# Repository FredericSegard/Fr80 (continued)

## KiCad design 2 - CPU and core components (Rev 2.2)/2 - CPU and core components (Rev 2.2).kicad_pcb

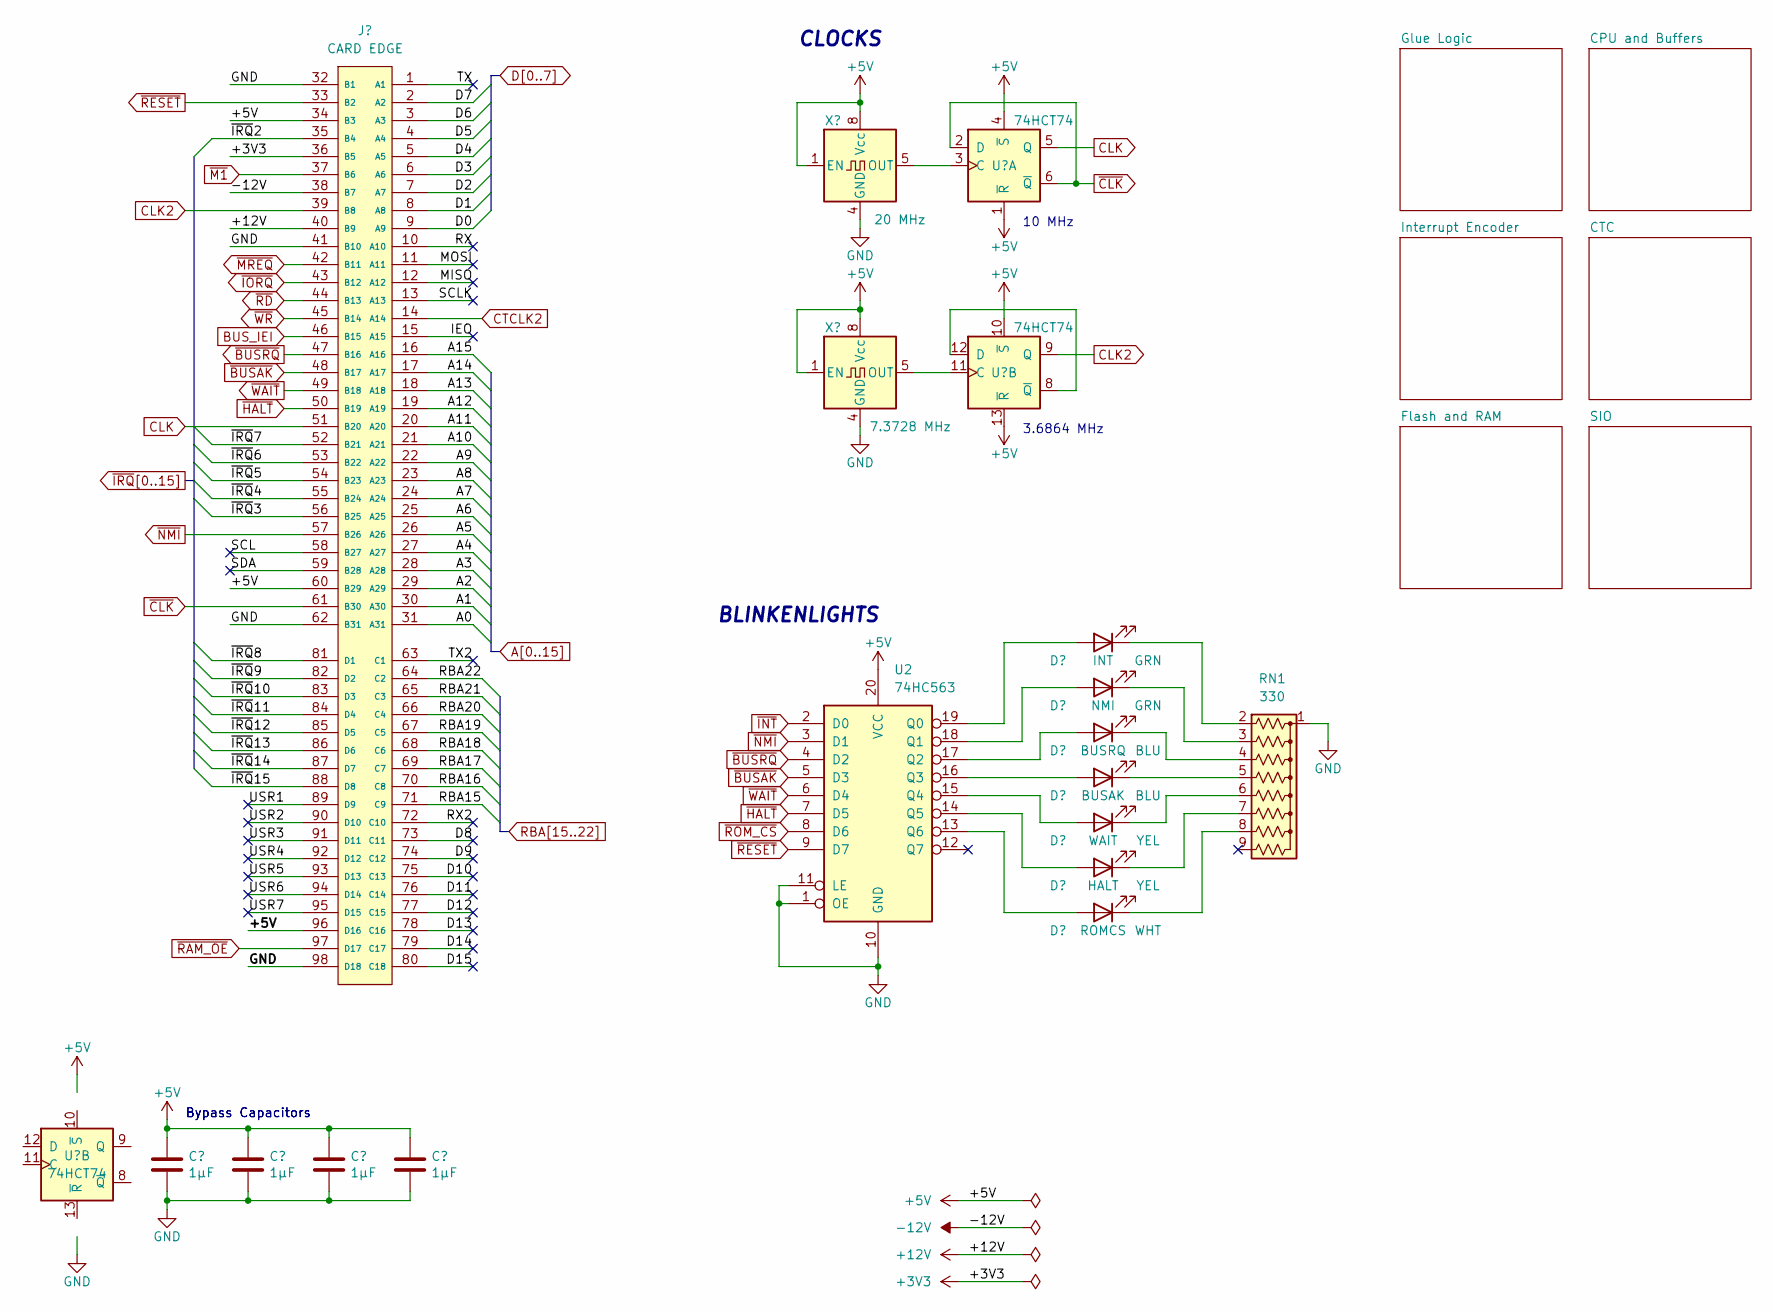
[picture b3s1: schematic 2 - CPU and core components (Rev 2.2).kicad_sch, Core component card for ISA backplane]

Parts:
C1, C2, C3, C4: 1µF; C_Disc_D3.4mm_W2.1mm_P2.50mm
D1: INT; LED_D3.0mm_Horizontal_O1.27mm_Z2.0mm_Clear
D2: NMI; LED_D3.0mm_Horizontal_O1.27mm_Z2.0mm_Clear
D3: BUSRQ; LED_D3.0mm_Horizontal_O1.27mm_Z2.0mm_Clear
D4: BUSAK; LED_D3.0mm_Horizontal_O1.27mm_Z2.0mm_Clear
D5: WAIT; LED_D3.0mm_Horizontal_O1.27mm_Z2.0mm_Clear
D6: HALT; LED_D3.0mm_Horizontal_O1.27mm_Z2.0mm_Clear
D7: ROMCS; LED_D3.0mm_Horizontal_O1.27mm_Z2.0mm_Clear
J1: CARD EDGE; BUS_AT v2
RN1: 330; R_Array_SIP9
U1: 74HCT74; DIP-14_W7.62mm_Socket
U2: 74HC563; DIP-20_W7.62mm_Socket
X1: 20 MHz; DIP-8-4_W7.62mm_Oscillator_Socket
X2: 7.3728 MHz; DIP-8-4_W7.62mm_Oscillator_Socket

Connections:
+3V3: J1.36 (B5)
+5V: C1.1, C2.1, C3.1, C4.1, J1.34 (B3), J1.60 (B29), J1.96 (D16), U1.1 (~R), U1.4 (~S), U1.10 (~S), U1.13 (~R), U1.14 (VCC), U2.20 (VCC), X1.1 (EN), X1.8 (Vcc), X2.1 (EN), X2.8 (Vcc); also elsewhere on the board
+12V: J1.40 (B9)
-12V: J1.38 (B7)
/D8: J1.73 (C11)
/D9: J1.74 (C12)
/D10: J1.75 (C13)
/D11: J1.76 (C14)
/D12: J1.77 (C15)
/D13: J1.78 (C16)
/D14: J1.79 (C17)
/D15: J1.80 (C18)
/IEO: J1.15 (A15)
/MISO: J1.12 (A12)
/MOSI: J1.11 (A11)
/RX: J1.10 (A10)
/RX2: J1.72 (C10)
/SCL: J1.58 (B27)
/SCLK: J1.13 (A13)
/SDA: J1.59 (B28)
/TX: J1.1 (A1)
/TX2: J1.63 (C1)
/USR1: J1.89 (D9)
/USR2: J1.90 (D10)
/USR3: J1.91 (D11)
/USR4: J1.92 (D12)
/USR5: J1.93 (D13)
/USR6: J1.94 (D14)
/USR7: J1.95 (D15)
A0: J1.31 (A31); also elsewhere on the board
A1: J1.30 (A30); also elsewhere on the board
A2: J1.29 (A29); also elsewhere on the board
A3: J1.28 (A28); also elsewhere on the board
A4: J1.27 (A27); also elsewhere on the board
A5: J1.26 (A26); also elsewhere on the board
A6: J1.25 (A25); also elsewhere on the board
A7: J1.24 (A24); also elsewhere on the board
A8: J1.23 (A23); also elsewhere on the board
A9: J1.22 (A22); also elsewhere on the board
A10: J1.21 (A21); also elsewhere on the board
A11: J1.20 (A20); also elsewhere on the board
A12: J1.19 (A19); also elsewhere on the board
A13: J1.18 (A18); also elsewhere on the board
A14: J1.17 (A17); also elsewhere on the board
A15: J1.16 (A16); also elsewhere on the board
BUS_IEI: J1.46 (B15); also elsewhere on the board
CLK: J1.51 (B20), U1.5 (Q); also elsewhere on the board
CLK2: J1.39 (B8), U1.9 (Q); also elsewhere on the board
CTCLK2: J1.14 (A14); also elsewhere on the board
D0: J1.9 (A9); also elsewhere on the board
D1: J1.8 (A8); also elsewhere on the board
D2: J1.7 (A7); also elsewhere on the board
D3: J1.6 (A6); also elsewhere on the board
D4: J1.5 (A5); also elsewhere on the board
D5: J1.4 (A4); also elsewhere on the board
D6: J1.3 (A3); also elsewhere on the board
D7: J1.2 (A2); also elsewhere on the board
GND: C1.2, C2.2, C3.2, C4.2, J1.32 (B1), J1.41 (B10), J1.62 (B31), J1.98 (D18), RN1.1 (common), U1.7 (GND), U2.1 (OE), U2.10 (GND), U2.11 (LE), X1.4 (GND), X2.4 (GND); also elsewhere on the board
unnamed: D1.2 (A), U2.19 (Q0)
unnamed: D1.1 (K), RN1.2 (R1)
unnamed: D2.2 (A), U2.18 (Q1)
unnamed: D2.1 (K), RN1.3 (R2)
unnamed: D3.2 (A), U2.17 (Q2)
unnamed: D3.1 (K), RN1.4 (R3)
unnamed: D4.2 (A), U2.16 (Q3)
unnamed: D4.1 (K), RN1.5 (R4)
unnamed: D5.2 (A), U2.15 (Q4)
unnamed: D5.1 (K), RN1.6 (R5)
unnamed: D6.2 (A), U2.14 (Q5)
unnamed: D6.1 (K), RN1.7 (R6)
unnamed: D7.2 (A), U2.13 (Q6)
unnamed: D7.1 (K), RN1.8 (R7)
unnamed: U1.3 (C), X1.5 (OUT)
unnamed: U1.11 (C), X2.5 (OUT)
unnamed: U1.8 (~Q), U1.12 (D)
RBA15: J1.71 (C9); also elsewhere on the board
RBA16: J1.70 (C8); also elsewhere on the board
RBA17: J1.69 (C7); also elsewhere on the board
RBA18: J1.68 (C6); also elsewhere on the board
RBA19: J1.67 (C5); also elsewhere on the board
RBA20: J1.66 (C4); also elsewhere on the board
RBA21: J1.65 (C3); also elsewhere on the board
RBA22: J1.64 (C2); also elsewhere on the board
~BUSAK: J1.48 (B17), U2.5 (D3); also elsewhere on the board
~BUSRQ: J1.47 (B16), U2.4 (D2); also elsewhere on the board
~CLK: J1.61 (B30), U1.2 (D), U1.6 (~Q)
~HALT: J1.50 (B19), U2.7 (D5); also elsewhere on the board
~INT: U2.2 (D0); also elsewhere on the board
~IORQ: J1.43 (B12); also elsewhere on the board
~IRQ2: J1.35 (B4); also elsewhere on the board
~IRQ3: J1.56 (B25); also elsewhere on the board
~IRQ4: J1.55 (B24); also elsewhere on the board
~IRQ5: J1.54 (B23); also elsewhere on the board
~IRQ6: J1.53 (B22); also elsewhere on the board
~IRQ7: J1.52 (B21); also elsewhere on the board
~IRQ8: J1.81 (D1); also elsewhere on the board
~IRQ9: J1.82 (D2); also elsewhere on the board
~IRQ10: J1.83 (D3); also elsewhere on the board
~IRQ11: J1.84 (D4); also elsewhere on the board
~IRQ12: J1.85 (D5); also elsewhere on the board
~IRQ13: J1.86 (D6); also elsewhere on the board
~IRQ14: J1.87 (D7); also elsewhere on the board
~IRQ15: J1.88 (D8); also elsewhere on the board
~M1: J1.37 (B6); also elsewhere on the board
~MREQ: J1.42 (B11); also elsewhere on the board
~NMI: J1.57 (B26), U2.3 (D1); also elsewhere on the board
~RAM_OE: J1.97 (D17); also elsewhere on the board
~RD: J1.44 (B13); also elsewhere on the board
~RESET: J1.33 (B2), U2.9 (D7); also elsewhere on the board
~ROM_CS: U2.8 (D6); also elsewhere on the board
~WAIT: J1.49 (B18), U2.6 (D4); also elsewhere on the board
~WR: J1.45 (B14); also elsewhere on the board

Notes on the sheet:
10 MHz
Bypass Capacitors
BLINKENLIGHTS
CLOCKS
3.6864 MHz

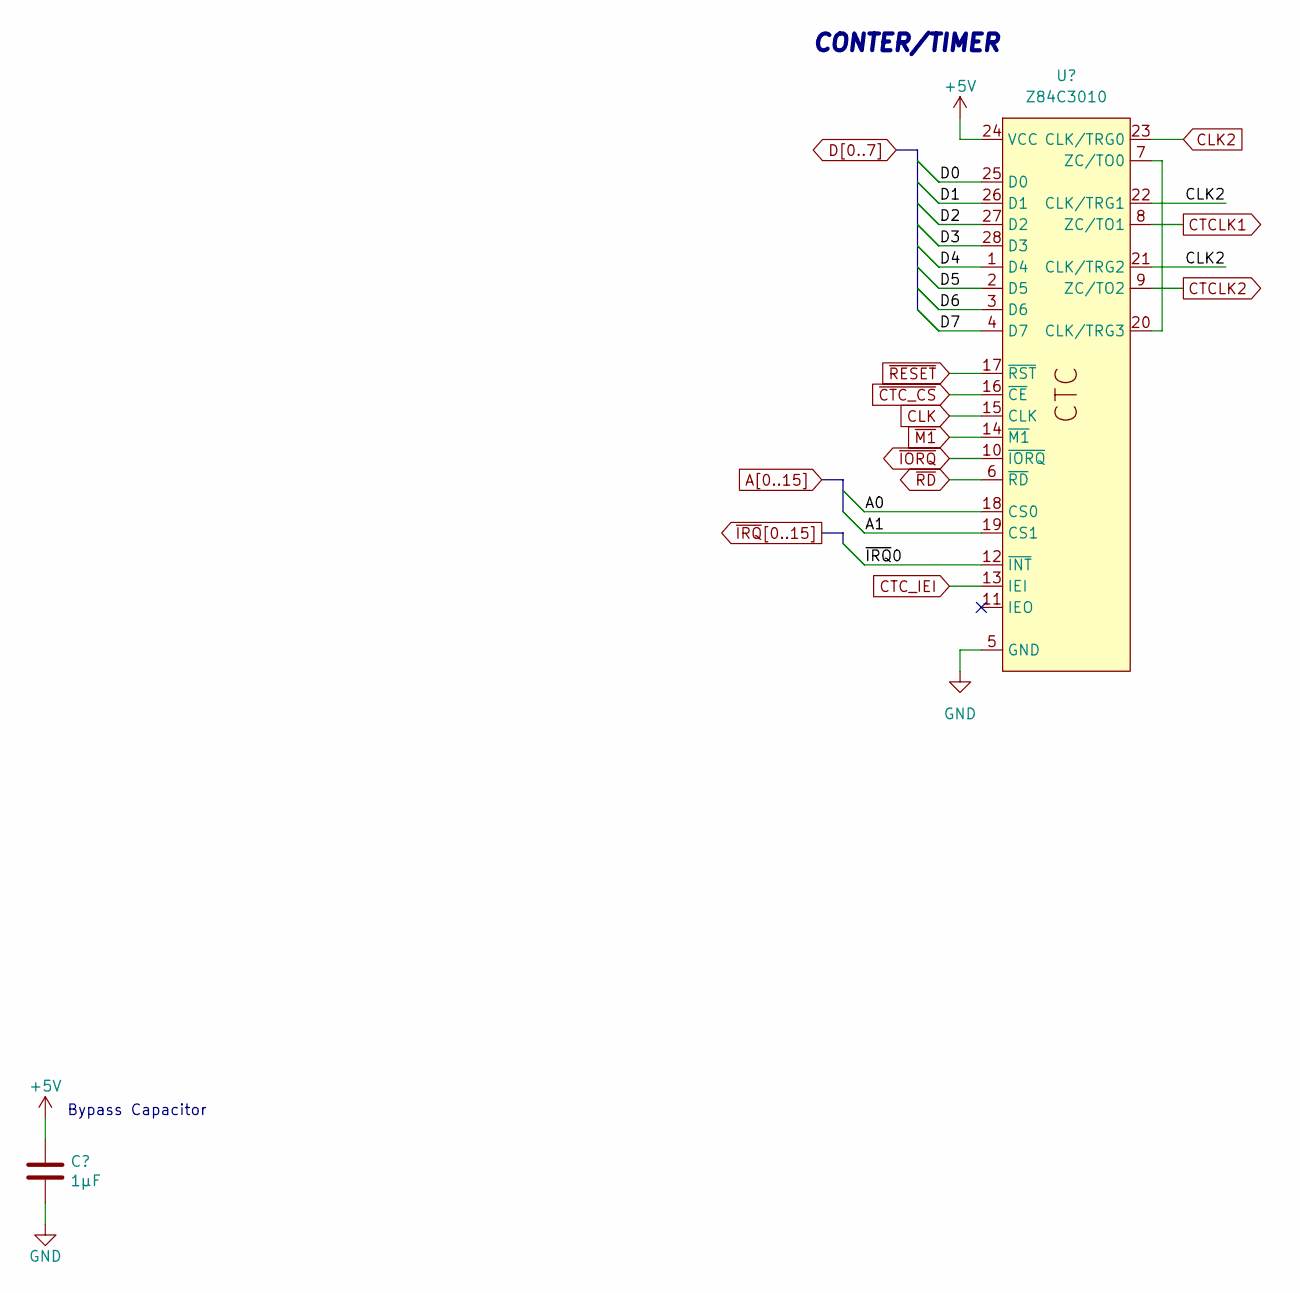
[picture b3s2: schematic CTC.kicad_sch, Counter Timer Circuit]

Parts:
C25: 1µF; C_Disc_D3.4mm_W2.1mm_P2.50mm
U21: Z84C3010; DIP-28_W15.24mm_Socket

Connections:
+5V: C25.1, U21.24 (VCC); also elsewhere on the board
A0: U21.18 (CS0); also elsewhere on the board
A1: U21.19 (CS1); also elsewhere on the board
CLK: U21.15 (CLK); also elsewhere on the board
CLK2: U21.21 (CLK/TRG2), U21.22 (CLK/TRG1), U21.23 (CLK/TRG0); also elsewhere on the board
CTCLK1: U21.8 (ZC/TO1); also elsewhere on the board
CTCLK2: U21.9 (ZC/TO2); also elsewhere on the board
CTC_IEI: U21.13 (IEI); also elsewhere on the board
D0: U21.25 (D0); also elsewhere on the board
D1: U21.26 (D1); also elsewhere on the board
D2: U21.27 (D2); also elsewhere on the board
D3: U21.28 (D3); also elsewhere on the board
D4: U21.1 (D4); also elsewhere on the board
D5: U21.2 (D5); also elsewhere on the board
D6: U21.3 (D6); also elsewhere on the board
D7: U21.4 (D7); also elsewhere on the board
GND: C25.2, U21.5 (GND); also elsewhere on the board
unnamed: U21.7 (ZC/TO0), U21.20 (CLK/TRG3)
~CTC_CS: U21.16 (~CE); also elsewhere on the board
~IORQ: U21.10 (~IORQ); also elsewhere on the board
~IRQ0: U21.12 (~INT); also elsewhere on the board
~M1: U21.14 (~M1); also elsewhere on the board
~RD: U21.6 (~RD); also elsewhere on the board
~RESET: U21.17 (~RST); also elsewhere on the board

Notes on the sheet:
CONTER/TIMER
Bypass Capacitor

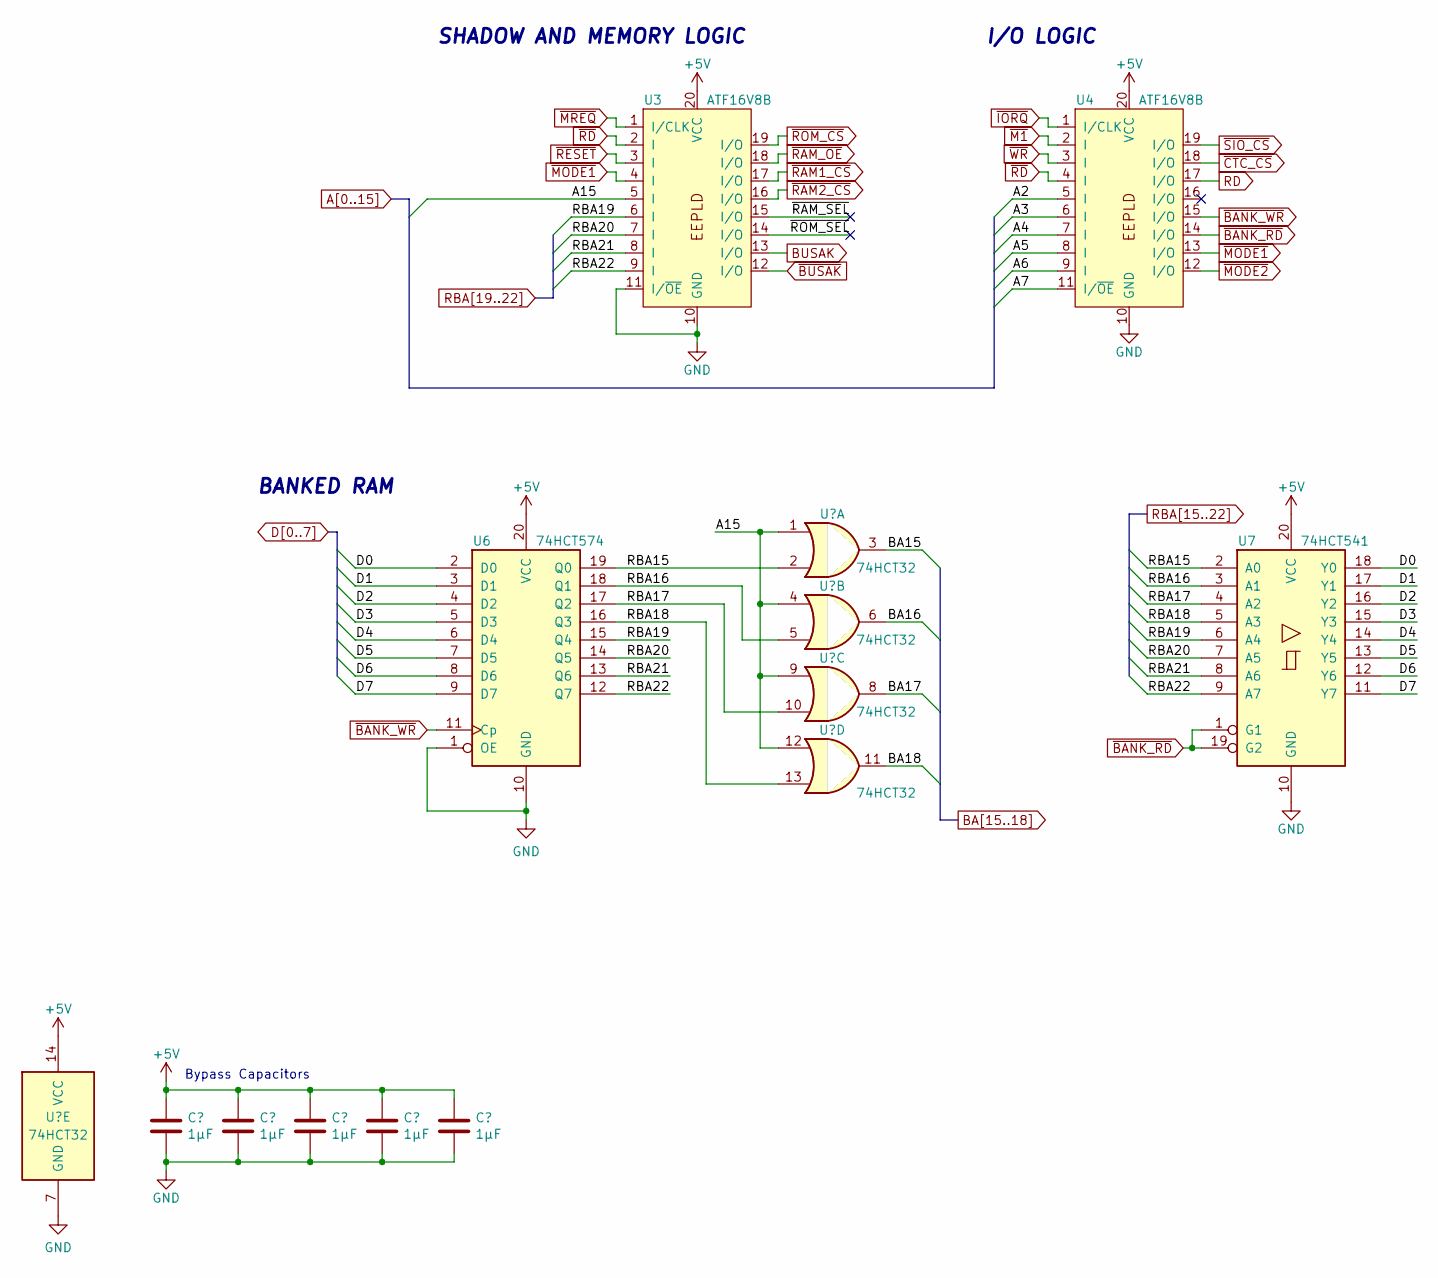
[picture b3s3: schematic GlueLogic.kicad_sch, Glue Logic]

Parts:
C5, C6, C7: 1µF; C_Disc_D3.0mm_W1.6mm_P2.50mm
C8, C9: 1µF; C_Disc_D3.0mm_W2.0mm_P2.50mm
U3, U4: ATF16V8B; DIP-20_W7.62mm_Socket
U5: 74HCT32; DIP-14_W7.62mm_Socket
U6: 74HCT574; DIP-20_W7.62mm_Socket
U7: 74HCT541; DIP-20_W7.62mm_Socket

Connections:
+5V: C5.1, C6.1, C7.1, C8.1, C9.1, U3.20 (VCC), U4.20 (VCC), U5.14 (VCC), U6.20 (VCC), U7.20 (VCC); also elsewhere on the board
/Glue Logic/~RAM_SEL: U3.15 (I/O)
/Glue Logic/~ROM_SEL: U3.14 (I/O)
A2: U4.5 (I); also elsewhere on the board
A3: U4.6 (I); also elsewhere on the board
A4: U4.7 (I); also elsewhere on the board
A5: U4.8 (I); also elsewhere on the board
A6: U4.9 (I); also elsewhere on the board
A7: U4.11 (I/~OE); also elsewhere on the board
A15: U3.5 (I), U5.1, U5.4, U5.9, U5.12; also elsewhere on the board
BA15: U5.3; also elsewhere on the board
BA16: U5.6; also elsewhere on the board
BA17: U5.8; also elsewhere on the board
BA18: U5.11; also elsewhere on the board
BUSAK: U3.13 (I/O); also elsewhere on the board
D0: U6.2 (D0), U7.18 (Y0); also elsewhere on the board
D1: U6.3 (D1), U7.17 (Y1); also elsewhere on the board
D2: U6.4 (D2), U7.16 (Y2); also elsewhere on the board
D3: U6.5 (D3), U7.15 (Y3); also elsewhere on the board
D4: U6.6 (D4), U7.14 (Y4); also elsewhere on the board
D5: U6.7 (D5), U7.13 (Y5); also elsewhere on the board
D6: U6.8 (D6), U7.12 (Y6); also elsewhere on the board
D7: U6.9 (D7), U7.11 (Y7); also elsewhere on the board
GND: C5.2, C6.2, C7.2, C8.2, C9.2, U3.10 (GND), U3.11 (I/~OE), U4.10 (GND), U5.7 (GND), U6.1 (OE), U6.10 (GND), U7.10 (GND); also elsewhere on the board
RBA15: U5.2, U6.19 (Q0), U7.2 (A0); also elsewhere on the board
RBA16: U5.5, U6.18 (Q1), U7.3 (A1); also elsewhere on the board
RBA17: U5.10, U6.17 (Q2), U7.4 (A2); also elsewhere on the board
RBA18: U5.13, U6.16 (Q3), U7.5 (A3); also elsewhere on the board
RBA19: U3.6 (I), U6.15 (Q4), U7.6 (A4); also elsewhere on the board
RBA20: U3.7 (I), U6.14 (Q5), U7.7 (A5); also elsewhere on the board
RBA21: U3.8 (I), U6.13 (Q6), U7.8 (A6); also elsewhere on the board
RBA22: U3.9 (I), U6.12 (Q7), U7.9 (A7); also elsewhere on the board
RD: U4.17 (I/O); also elsewhere on the board
~BANK_RD: U4.14 (I/O), U7.1 (G1), U7.19 (G2)
~BANK_WR: U4.15 (I/O), U6.11 (Cp)
~BUSAK: U3.12 (I/O); also elsewhere on the board
~CTC_CS: U4.18 (I/O); also elsewhere on the board
~IORQ: U4.1 (I/CLK); also elsewhere on the board
~M1: U4.2 (I); also elsewhere on the board
~MODE1: U3.4 (I), U4.13 (I/O); also elsewhere on the board
~MODE2: U4.12 (I/O); also elsewhere on the board
~MREQ: U3.1 (I/CLK); also elsewhere on the board
~RAM1_CS: U3.17 (I/O); also elsewhere on the board
~RAM2_CS: U3.16 (I/O); also elsewhere on the board
~RAM_OE: U3.18 (I/O); also elsewhere on the board
~RD: U3.2 (I), U4.4 (I); also elsewhere on the board
~RESET: U3.3 (I); also elsewhere on the board
~ROM_CS: U3.19 (I/O); also elsewhere on the board
~SIO_CS: U4.19 (I/O); also elsewhere on the board
~WR: U4.3 (I); also elsewhere on the board

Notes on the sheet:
Bypass Capacitors
I/O LOGIC
BANKED RAM
SHADOW AND MEMORY LOGIC

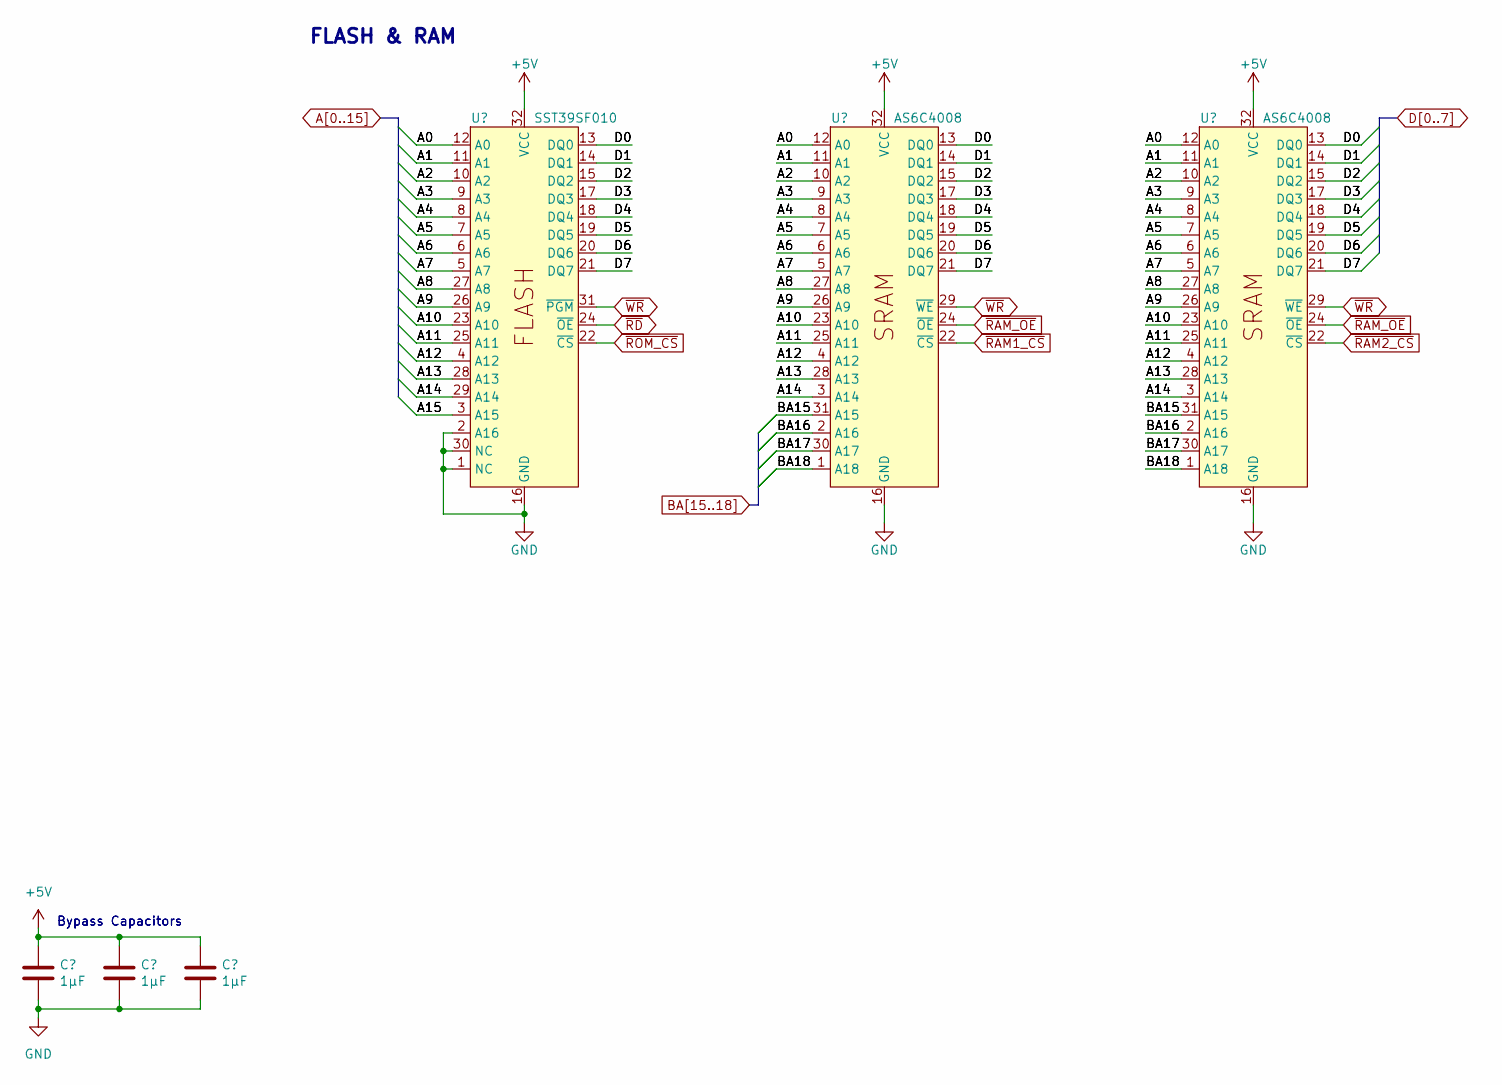
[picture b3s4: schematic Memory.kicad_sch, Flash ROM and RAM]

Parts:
C17, C18, C19: 1µF; C_Disc_D3.4mm_W2.1mm_P2.50mm
U15: SST39SF010; DIP-32_W15.24mm_Socket
U16, U17: AS6C4008; DIP-32_W15.24mm_Socket

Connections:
+5V: C17.1, C18.1, C19.1, U15.32 (VCC), U16.32 (VCC), U17.32 (VCC); also elsewhere on the board
A0: U15.12 (A0), U16.12 (A0), U17.12 (A0); also elsewhere on the board
A1: U15.11 (A1), U16.11 (A1), U17.11 (A1); also elsewhere on the board
A2: U15.10 (A2), U16.10 (A2), U17.10 (A2); also elsewhere on the board
A3: U15.9 (A3), U16.9 (A3), U17.9 (A3); also elsewhere on the board
A4: U15.8 (A4), U16.8 (A4), U17.8 (A4); also elsewhere on the board
A5: U15.7 (A5), U16.7 (A5), U17.7 (A5); also elsewhere on the board
A6: U15.6 (A6), U16.6 (A6), U17.6 (A6); also elsewhere on the board
A7: U15.5 (A7), U16.5 (A7), U17.5 (A7); also elsewhere on the board
A8: U15.27 (A8), U16.27 (A8), U17.27 (A8); also elsewhere on the board
A9: U15.26 (A9), U16.26 (A9), U17.26 (A9); also elsewhere on the board
A10: U15.23 (A10), U16.23 (A10), U17.23 (A10); also elsewhere on the board
A11: U15.25 (A11), U16.25 (A11), U17.25 (A11); also elsewhere on the board
A12: U15.4 (A12), U16.4 (A12), U17.4 (A12); also elsewhere on the board
A13: U15.28 (A13), U16.28 (A13), U17.28 (A13); also elsewhere on the board
A14: U15.29 (A14), U16.3 (A14), U17.3 (A14); also elsewhere on the board
A15: U15.3 (A15); also elsewhere on the board
BA15: U16.31 (A15), U17.31 (A15); also elsewhere on the board
BA16: U16.2 (A16), U17.2 (A16); also elsewhere on the board
BA17: U16.30 (A17), U17.30 (A17); also elsewhere on the board
BA18: U16.1 (A18), U17.1 (A18); also elsewhere on the board
D0: U15.13 (DQ0), U16.13 (DQ0), U17.13 (DQ0); also elsewhere on the board
D1: U15.14 (DQ1), U16.14 (DQ1), U17.14 (DQ1); also elsewhere on the board
D2: U15.15 (DQ2), U16.15 (DQ2), U17.15 (DQ2); also elsewhere on the board
D3: U15.17 (DQ3), U16.17 (DQ3), U17.17 (DQ3); also elsewhere on the board
D4: U15.18 (DQ4), U16.18 (DQ4), U17.18 (DQ4); also elsewhere on the board
D5: U15.19 (DQ5), U16.19 (DQ5), U17.19 (DQ5); also elsewhere on the board
D6: U15.20 (DQ6), U16.20 (DQ6), U17.20 (DQ6); also elsewhere on the board
D7: U15.21 (DQ7), U16.21 (DQ7), U17.21 (DQ7); also elsewhere on the board
GND: C17.2, C18.2, C19.2, U15.1 (NC), U15.2 (A16), U15.16 (GND), U15.30 (NC), U16.16 (GND), U17.16 (GND); also elsewhere on the board
~RAM1_CS: U16.22 (~CS); also elsewhere on the board
~RAM2_CS: U17.22 (~CS); also elsewhere on the board
~RAM_OE: U16.24 (~OE), U17.24 (~OE); also elsewhere on the board
~RD: U15.24 (~OE); also elsewhere on the board
~ROM_CS: U15.22 (~CS); also elsewhere on the board
~WR: U15.31 (~PGM), U16.29 (~WE), U17.29 (~WE); also elsewhere on the board

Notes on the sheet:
Bypass Capacitors
FLASH & RAM

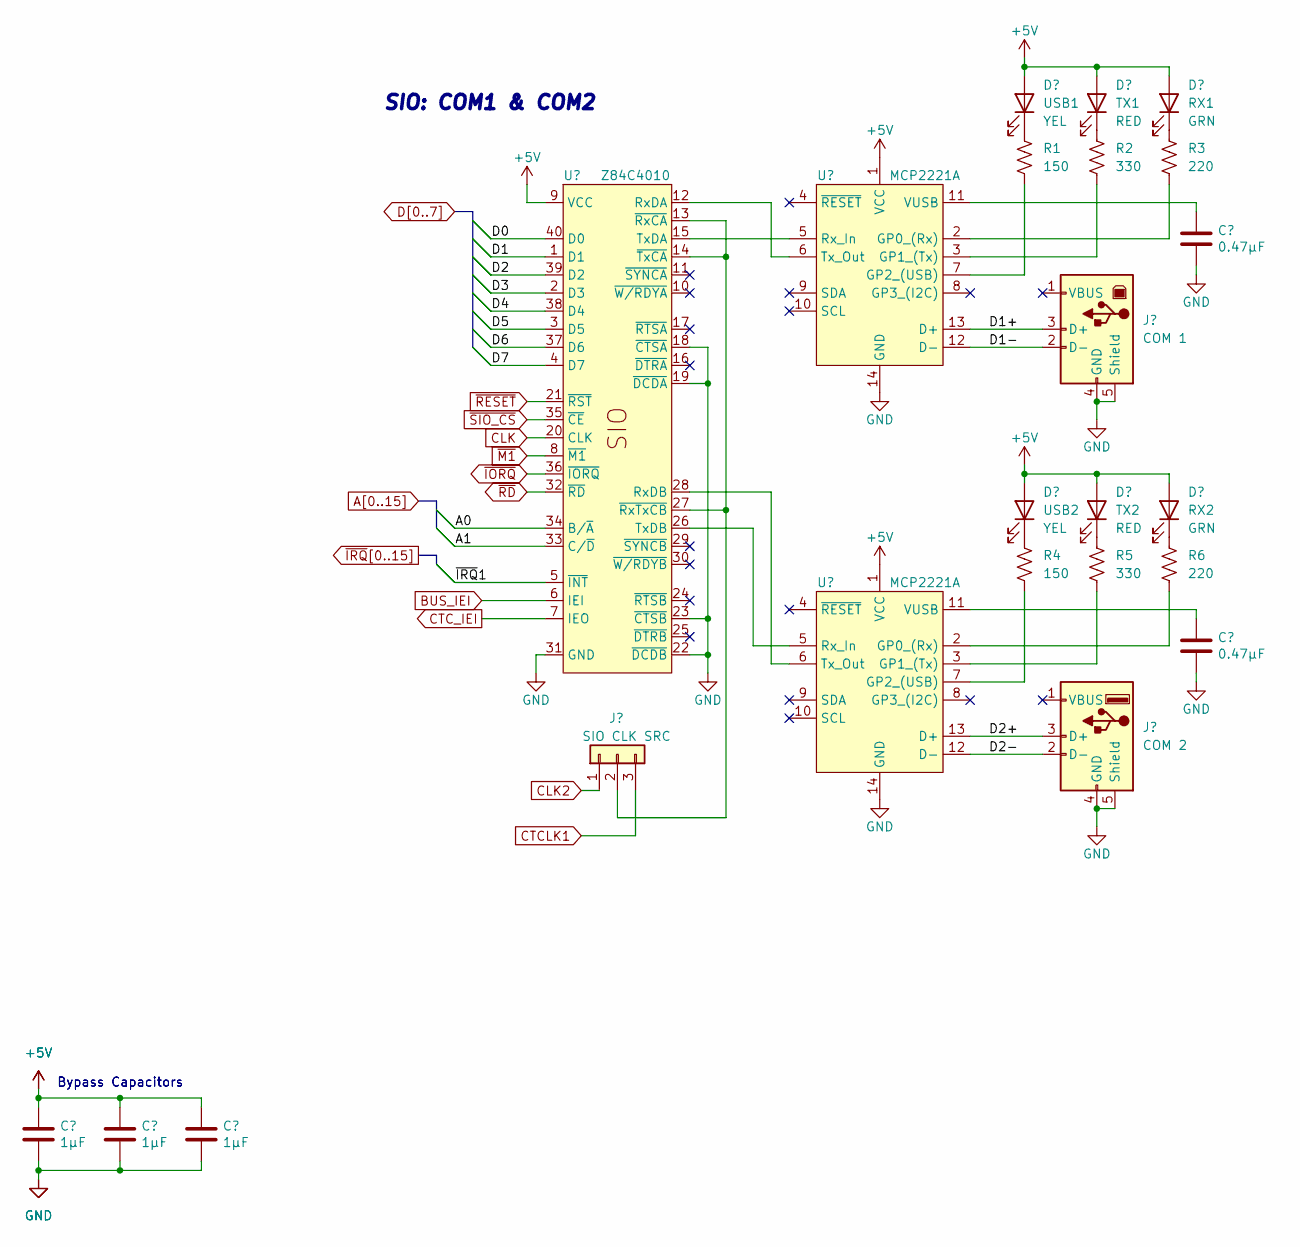
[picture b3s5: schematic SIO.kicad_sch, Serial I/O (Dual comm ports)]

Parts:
C20, C21: 0.47µF; C_Disc_D3.4mm_W2.1mm_P2.50mm
C22, C23, C24: 1µF; C_Disc_D3.4mm_W2.1mm_P2.50mm
D8: USB1; LED_D3.0mm_Horizontal_O1.27mm_Z2.0mm_Clear
D9: TX1; LED_D3.0mm_Horizontal_O1.27mm_Z2.0mm_Clear
D10: RX1; LED_D3.0mm_Horizontal_O1.27mm_Z2.0mm_Clear
D11: USB2; LED_D3.0mm_Horizontal_O1.27mm_Z2.0mm_Clear
D12: TX2; LED_D3.0mm_Horizontal_O1.27mm_Z2.0mm_Clear
D13: RX2; LED_D3.0mm_Horizontal_O1.27mm_Z2.0mm_Clear
J3: COM 1; USB_B_Lumberg_2411_02_Horizontal
J4: COM 2; USB_A_Stewart_SS-52100-001_Horizontal
J5: SIO CLK SRC; PinHeader_1x03_P2.54mm_Vertical
R1, R4: 150; R_Axial_DIN0207_L6.3mm_D2.5mm_P10.16mm_Horizontal
R2, R5: 330; R_Axial_DIN0207_L6.3mm_D2.5mm_P10.16mm_Horizontal
R3, R6: 220; R_Axial_DIN0207_L6.3mm_D2.5mm_P10.16mm_Horizontal
U18: Z84C4010; DIP-40_W15.24mm_Socket
U19, U20: MCP2221A; DIP-14_W7.62mm_Socket

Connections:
+5V: C22.1, C23.1, C24.1, D8.2 (A), D9.2 (A), D10.2 (A), D11.2 (A), D12.2 (A), D13.2 (A), U18.9 (VCC), U19.1 (VCC), U20.1 (VCC); also elsewhere on the board
/SIO/D1+: J3.3 (D+), U19.13 (D+)
/SIO/D1-: J3.2 (D-), U19.12 (D-)
/SIO/D2+: J4.3 (D+), U20.13 (D+)
/SIO/D2-: J4.2 (D-), U20.12 (D-)
A0: U18.34 (B/~A); also elsewhere on the board
A1: U18.33 (C/~D); also elsewhere on the board
BUS_IEI: U18.6 (IEI); also elsewhere on the board
CLK: U18.20 (CLK); also elsewhere on the board
CLK2: J5.1; also elsewhere on the board
CTCLK1: J5.3; also elsewhere on the board
CTC_IEI: U18.7 (IEO); also elsewhere on the board
D0: U18.40 (D0); also elsewhere on the board
D1: U18.1 (D1); also elsewhere on the board
D2: U18.39 (D2); also elsewhere on the board
D3: U18.2 (D3); also elsewhere on the board
D4: U18.38 (D4); also elsewhere on the board
D5: U18.3 (D5); also elsewhere on the board
D6: U18.37 (D6); also elsewhere on the board
D7: U18.4 (D7); also elsewhere on the board
GND: C20.2, C21.2, C22.2, C23.2, C24.2, J3.4 (GND), J3.5 (Shield), J4.4 (GND), J4.5 (Shield), U18.18 (~CTSA), U18.19 (~DCDA), U18.22 (~DCDB), U18.23 (~CTSB), U18.31 (GND), U19.14 (GND), U20.14 (GND); also elsewhere on the board
unnamed: D8.1 (K), R1.1
unnamed: D9.1 (K), R2.1
unnamed: D10.1 (K), R3.1
unnamed: D11.1 (K), R4.1
unnamed: D12.1 (K), R5.1
unnamed: D13.1 (K), R6.1
unnamed: J5.2, U18.13 (~RxCA), U18.14 (~TxCA), U18.27 (~RxTxCB)
unnamed: U18.12 (RxDA), U19.6 (Tx_Out)
unnamed: U18.28 (RxDB), U20.6 (Tx_Out)
unnamed: U18.15 (TxDA), U19.5 (Rx_In)
unnamed: U18.26 (TxDB), U20.5 (Rx_In)
unnamed: R3.2, U19.2 (GP0_(Rx))
unnamed: R2.2, U19.3 (GP1_(Tx))
unnamed: R1.2, U19.7 (GP2_(USB))
unnamed: C20.1, U19.11 (VUSB)
unnamed: R6.2, U20.2 (GP0_(Rx))
unnamed: R5.2, U20.3 (GP1_(Tx))
unnamed: R4.2, U20.7 (GP2_(USB))
unnamed: C21.1, U20.11 (VUSB)
~IORQ: U18.36 (~IORQ); also elsewhere on the board
~IRQ1: U18.5 (~INT); also elsewhere on the board
~M1: U18.8 (~M1); also elsewhere on the board
~RD: U18.32 (~RD); also elsewhere on the board
~RESET: U18.21 (~RST); also elsewhere on the board
~SIO_CS: U18.35 (~CE); also elsewhere on the board

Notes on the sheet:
SIO: COM1 & COM2
Bypass Capacitors

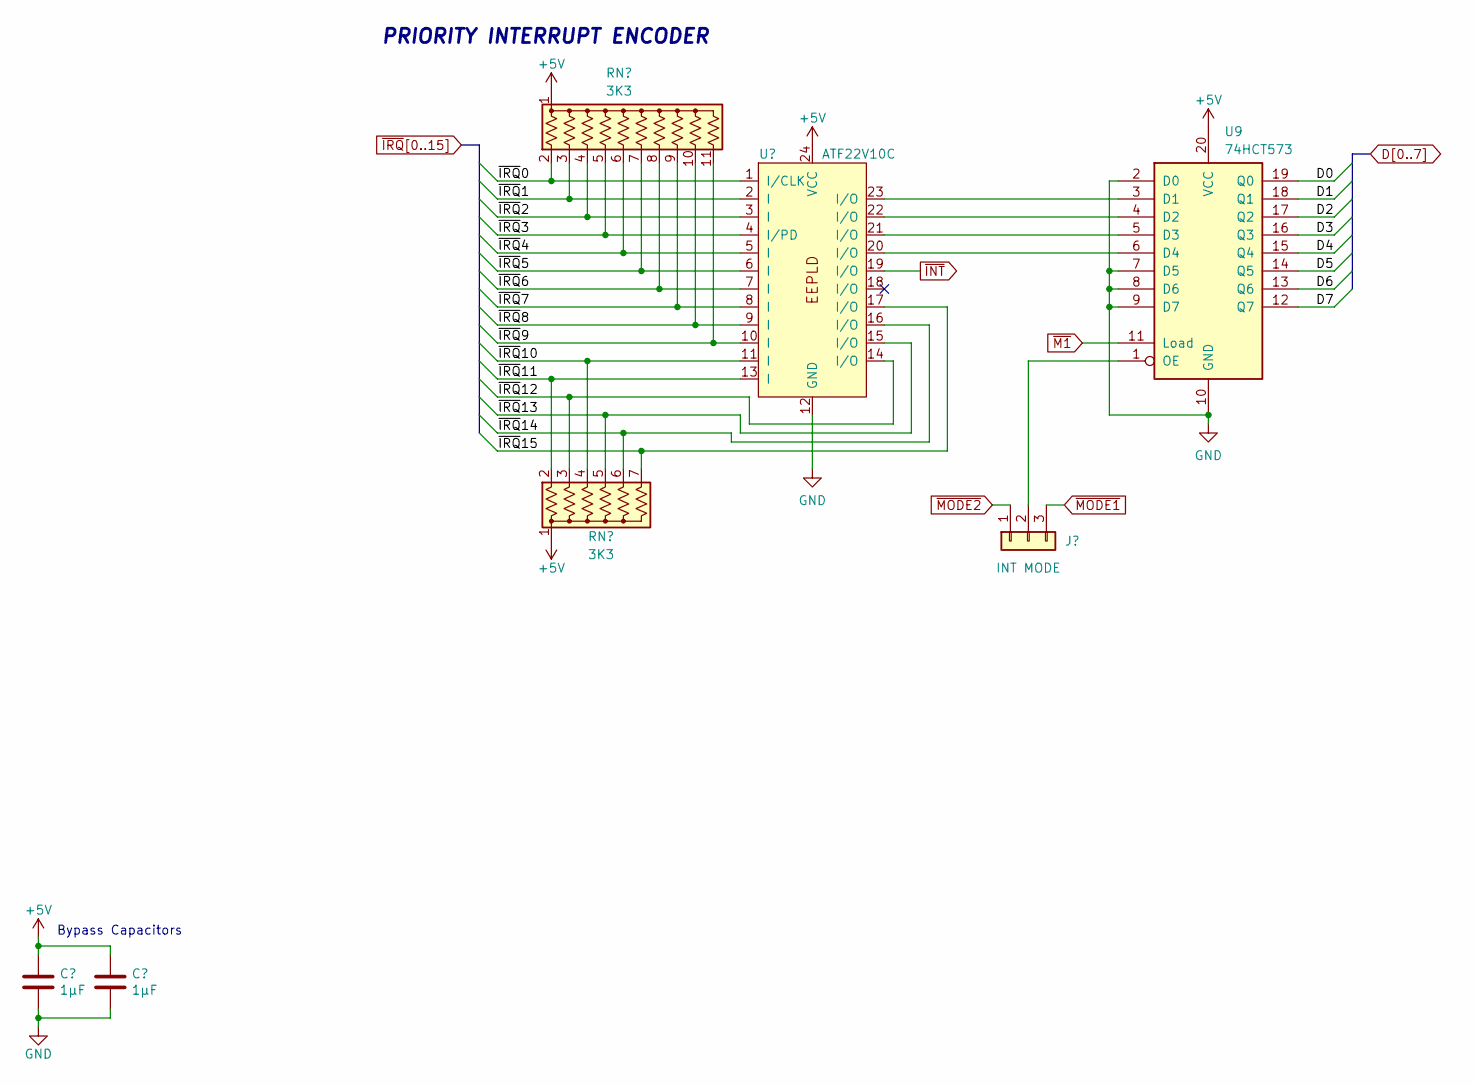
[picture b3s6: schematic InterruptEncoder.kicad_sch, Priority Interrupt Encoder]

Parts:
C10, C11: 1µF; C_Disc_D3.0mm_W1.6mm_P2.50mm
J2: INT MODE; PinHeader_1x03_P2.54mm_Vertical
RN2: 3K3; R_Array_SIP11
RN3: 3K3; R_Array_SIP7
U8: ATF22V10C; DIP-24_W7.62mm_Socket
U9: 74HCT573; DIP-20_W7.62mm_Socket

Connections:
+5V: C10.1, C11.1, RN2.1 (common), RN3.1 (common), U8.24 (VCC), U9.20 (VCC); also elsewhere on the board
D0: U9.19 (Q0); also elsewhere on the board
D1: U9.18 (Q1); also elsewhere on the board
D2: U9.17 (Q2); also elsewhere on the board
D3: U9.16 (Q3); also elsewhere on the board
D4: U9.15 (Q4); also elsewhere on the board
D5: U9.14 (Q5); also elsewhere on the board
D6: U9.13 (Q6); also elsewhere on the board
D7: U9.12 (Q7); also elsewhere on the board
GND: C10.2, C11.2, U8.12 (GND), U9.2 (D0), U9.7 (D5), U9.8 (D6), U9.9 (D7), U9.10 (GND); also elsewhere on the board
unnamed: J2.2, U9.1 (OE)
unnamed: U8.23 (I/O), U9.3 (D1)
unnamed: U8.22 (I/O), U9.4 (D2)
unnamed: U8.21 (I/O), U9.5 (D3)
unnamed: U8.20 (I/O), U9.6 (D4)
~INT: U8.19 (I/O); also elsewhere on the board
~IRQ0: RN2.2 (R1), U8.1 (I/CLK); also elsewhere on the board
~IRQ1: RN2.3 (R2), U8.2 (I); also elsewhere on the board
~IRQ2: RN2.4 (R3), U8.3 (I); also elsewhere on the board
~IRQ3: RN2.5 (R4), U8.4 (I/PD); also elsewhere on the board
~IRQ4: RN2.6 (R5), U8.5 (I); also elsewhere on the board
~IRQ5: RN2.7 (R6), U8.6 (I); also elsewhere on the board
~IRQ6: RN2.8 (R7), U8.7 (I); also elsewhere on the board
~IRQ7: RN2.9 (R8), U8.8 (I); also elsewhere on the board
~IRQ8: RN2.10 (R9), U8.9 (I); also elsewhere on the board
~IRQ9: RN2.11 (R10), U8.10 (I); also elsewhere on the board
~IRQ10: RN3.4 (R3), U8.11 (I); also elsewhere on the board
~IRQ11: RN3.2 (R1), U8.13 (I); also elsewhere on the board
~IRQ12: RN3.3 (R2), U8.14 (I/O); also elsewhere on the board
~IRQ13: RN3.5 (R4), U8.15 (I/O); also elsewhere on the board
~IRQ14: RN3.6 (R5), U8.16 (I/O); also elsewhere on the board
~IRQ15: RN3.7 (R6), U8.17 (I/O); also elsewhere on the board
~M1: U9.11 (Load); also elsewhere on the board
~MODE1: J2.3; also elsewhere on the board
~MODE2: J2.1; also elsewhere on the board

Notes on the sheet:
Bypass Capacitors
PRIORITY INTERRUPT ENCODER
